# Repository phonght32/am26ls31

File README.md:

# robotic-lspb-control-step-motor-hardware

### Schematic 

### PCB

### 3D

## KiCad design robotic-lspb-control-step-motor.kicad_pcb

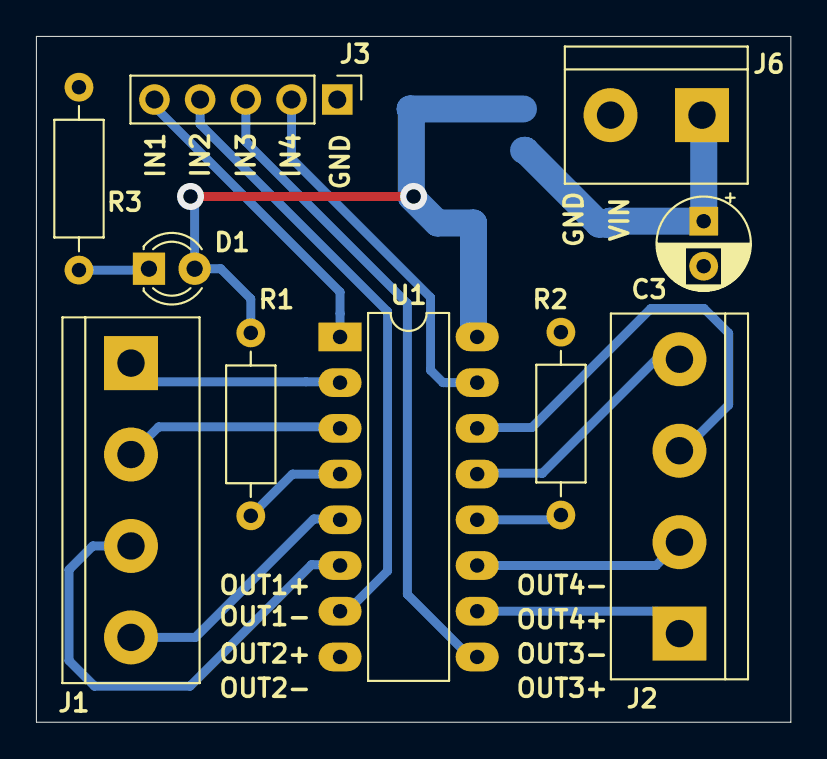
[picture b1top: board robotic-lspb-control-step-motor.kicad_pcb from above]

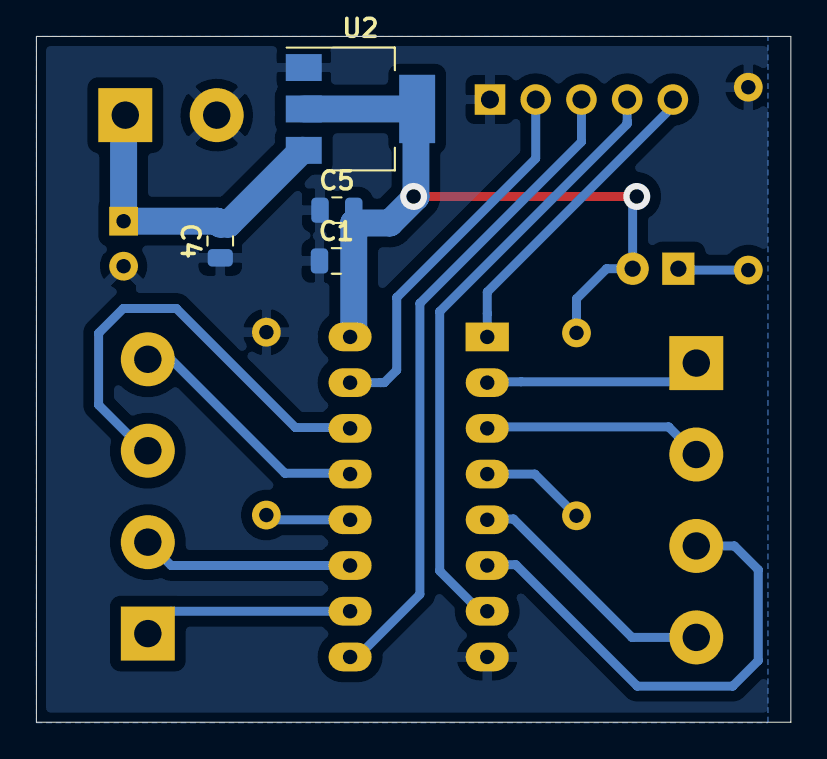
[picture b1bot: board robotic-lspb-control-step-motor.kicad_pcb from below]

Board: 2 copper layers, 41.9 x 38.1 mm, 14 parts (4 on the bottom side), 18 nets.

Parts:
C1, C4, C5: 100nF; C_0805_2012Metric
C3: 10uF; CP_Radial_D5.0mm_P2.50mm
D1: LED_Small; LED_D3.0mm
J1: DRV1; TerminalBlock_bornier-4_P5.08mm
J2: DRV2; TerminalBlock_bornier-4_P5.08mm
J3: Conn_01x05; PinHeader_1x05_P2.54mm_Vertical
J6: VIN; TerminalBlock_bornier-2_P5.08mm
R1, R2, R3: R_Small; R_Axial_DIN0207_L6.3mm_D2.5mm_P10.16mm_Horizontal
U1: AM26LS31x; DIP-16_W7.62mm_LongPads
U2: AMS1117-5.0; SOT-223-3_TabPin2

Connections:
+5V: C1.2, C5.2, D1.2, R1.2, U1.16, U2.2
DRV1_DIR: J3.4, U1.7
DRV1_DIR_N: J1.4, U1.5
DRV1_DIR_P: J1.3, U1.6
DRV1_PULSE: J3.5, U1.1
DRV1_PULSE_N: J1.2, U1.3
DRV1_PULSE_P: J1.1, U1.2
DRV2_DIR: J3.2, U1.15
DRV2_DIR_N: J2.4, U1.13
DRV2_DIR_P: J2.3, U1.14
DRV2_PULSE: J3.3, U1.9
DRV2_PULSE_N: J2.2, U1.11
DRV2_PULSE_P: J2.1, U1.10
GND: C1.1, C3.2, C4.1, C5.1, J3.1, J6.2, R2.2, R3.2, U1.8, U2.1
unnamed: D1.1, R3.1
unnamed: R1.1, U1.4
unnamed: R2.1, U1.12
VIN: C3.1, C4.2, J6.1, U2.3

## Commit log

2019-09-18 add image
